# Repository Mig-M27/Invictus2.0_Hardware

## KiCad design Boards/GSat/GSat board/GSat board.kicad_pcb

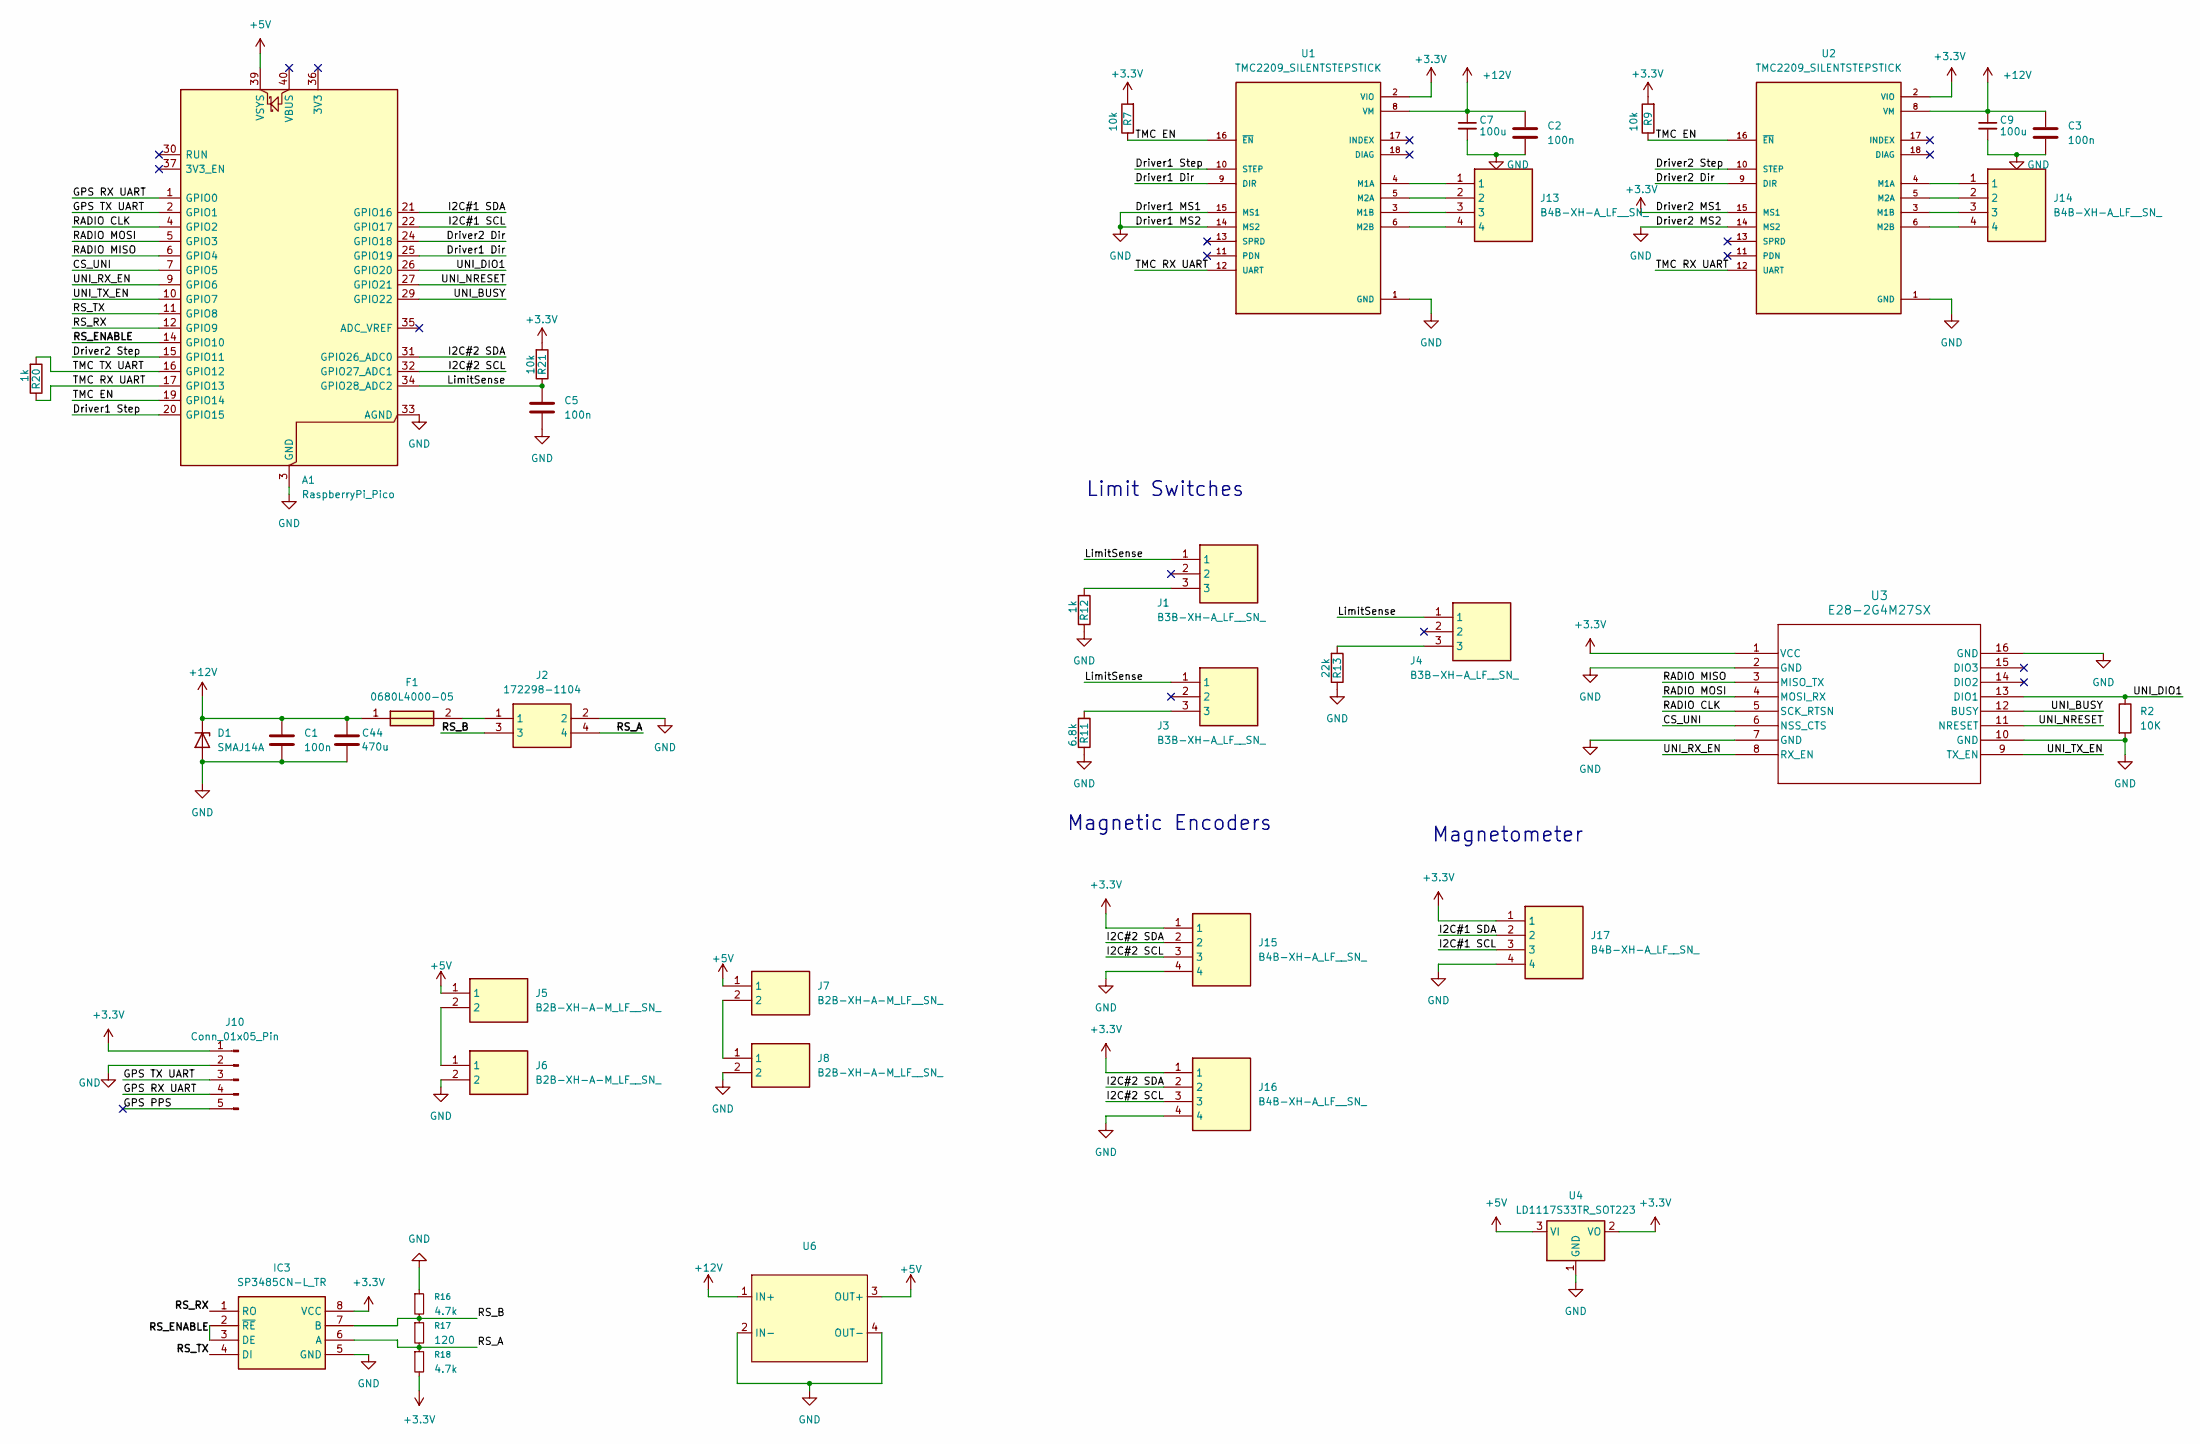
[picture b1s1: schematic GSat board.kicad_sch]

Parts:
A1: RaspberryPi_Pico; RaspberryPi_Pico_Common_Unspecified
C1, C2, C3, C5: 100n; C_0603_1608Metric_Pad1.08x0.95mm_HandSolder
C7, C9: 100u; CP_Elec_6.3x7.7
C44: 470u; CP_Elec_10x10
D1: SMAJ14A; D_SMB
F1: 0680L4000-05; Fuse_2512_6332Metric; Mouser Part Number 530-0ABB-6000-TM
IC3: SP3485CN-L_TR; SOIC127P600X175-8N; Mouser Part Number 701-SP3485CN-L/TR
J1, J3, J4: B3B-XH-A_LF__SN_; B3BXHALFSN; Mouser Part Number 306-B3BXHALFSNP
J2: 172298-1104; 172298-YY04; Mouser Part Number 538-172298-1104
J5, J6, J7, J8: B2B-XH-A-M_LF__SN_; B2BXHAMLFSN; Mouser Part Number 306-B2B-XH-A-MLFS
J10: Conn_01x05_Pin; PinSocket_1x05_P2.54mm_Vertical
J13, J14, J15, J16, J17: B4B-XH-A_LF__SN_; B4BXHALFSN; Mouser Part Number 306-B4BXHALFSN
R2: 10K; R_0603_1608Metric_Pad0.98x0.95mm_HandSolder
R7, R9, R21: 10k; R_0603_1608Metric_Pad0.98x0.95mm_HandSolder
R11: 6.8k; R_0603_1608Metric_Pad0.98x0.95mm_HandSolder
R12, R20: 1k; R_0603_1608Metric_Pad0.98x0.95mm_HandSolder
R13: 22k; R_0603_1608Metric_Pad0.98x0.95mm_HandSolder
R16, R18: 4.7k; R_0603_1608Metric_Pad0.98x0.95mm_HandSolder
R17: 120; R_0603_1608Metric_Pad0.98x0.95mm_HandSolder
U1, U2: TMC2209_SILENTSTEPSTICK; MODULE_TMC2209_SILENTSTEPSTICK; PARTREV 1.20
U3: E28-2G4M27SX; Radio_Module_PST
U4: LD1117S33TR_SOT223; SOT-223-3_TabPin2
U6: DCDC_Module

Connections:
+3.3V: IC3.8 (VCC), J10.1, J15.1, J16.1, J17.1, R7.2, R9.2, R18.2, R21.2, U1.2 (VIO), U2.2 (VIO), U2.15 (MS1), U3.1 (VCC), U4.2 (VO)
+5V: A1.39 (VSYS), J5.1, J7.1, U4.3 (VI), U6.3 (OUT+)
+12V: C1.1, C2.1, C3.1, C7.1, C9.1, C44.1, D1.1 (K), F1.1, U1.8 (VM), U2.8 (VM), U6.1 (IN+)
/CS_UNI: A1.7 (GPIO5), U3.6 (NSS_CTS)
/Driver1 Dir: A1.25 (GPIO19), U1.9 (DIR)
/Driver1 Step: A1.20 (GPIO15), U1.10 (STEP)
/Driver2 Dir: A1.24 (GPIO18), U2.9 (DIR)
/Driver2 Step: A1.15 (GPIO11), U2.10 (STEP)
/GPS PPS: J10.5
/GPS RX UART: A1.1 (GPIO0), J10.4
/GPS TX UART: A1.2 (GPIO1), J10.3
/I2C#1 SCL: A1.22 (GPIO17), J17.3
/I2C#1 SDA: A1.21 (GPIO16), J17.2
/I2C#2 SCL: A1.32 (GPIO27_ADC1), J15.3, J16.3
/I2C#2 SDA: A1.31 (GPIO26_ADC0), J15.2, J16.2
/LimitSense: A1.34 (GPIO28_ADC2), C5.1, J1.1, J3.1, J4.1, R21.1
/RADIO CLK: A1.4 (GPIO2), U3.5 (SCK_RTSN)
/RADIO MISO: A1.6 (GPIO4), U3.3 (MISO_TX)
/RADIO MOSI: A1.5 (GPIO3), U3.4 (MOSI_RX)
/RS_A: IC3.6 (A), J2.4, R17.2, R18.1
/RS_B: IC3.7 (B), J2.3, R16.2, R17.1
/RS_ENABLE: A1.14 (GPIO10), IC3.2 (~RE), IC3.3 (DE)
/RS_RX: A1.12 (GPIO9), IC3.1 (RO)
/RS_TX: A1.11 (GPIO8), IC3.4 (DI)
/TMC EN: A1.19 (GPIO14), R7.1, R9.1, U1.16 (~EN), U2.16 (~EN)
/TMC RX UART: A1.17 (GPIO13), R20.1, U1.12 (UART), U2.12 (UART)
/TMC TX UART: A1.16 (GPIO12), R20.2
/UNI_BUSY: A1.29 (GPIO22), U3.12 (BUSY)
/UNI_DIO1: A1.26 (GPIO20), R2.1, U3.13 (DIO1)
/UNI_NRESET: A1.27 (GPIO21), U3.11 (NRESET)
/UNI_RX_EN: A1.9 (GPIO6), U3.8 (RX_EN)
/UNI_TX_EN: A1.10 (GPIO7), U3.9 (TX_EN)
GND: A1.3 (GND), A1.8 (GND), A1.13 (GND), A1.18 (GND), A1.23 (GND), A1.28 (GND), A1.33 (AGND), A1.38 (GND), C1.2, C2.2, C3.2, C5.2, C7.2, C9.2, C44.2, D1.2 (A), IC3.5 (GND), J2.2, J6.2, J8.2, J10.2, J15.4, J16.4, J17.4, R2.2, R11.1, R12.1, R13.1, R16.1, U1.1 (GND), U1.7 (GND), U1.14 (MS2), U1.15 (MS1), U2.1 (GND), U2.7 (GND), U2.14 (MS2), U3.2 (GND), U3.7 (GND), U3.10 (GND), U3.16 (GND), U4.1 (GND), U6.2 (IN-), U6.4 (OUT-)
unnamed: F1.2, J2.1
unnamed: J1.3, R12.2
unnamed: J3.3, R11.2
unnamed: J4.3, R13.2
unnamed: J5.2, J6.1
unnamed: J7.2, J8.1
unnamed: J13.1, U1.4 (M1A)
unnamed: J13.3, U1.3 (M1B)
unnamed: J13.2, U1.5 (M2A)
unnamed: J13.4, U1.6 (M2B)
unnamed: J14.1, U2.4 (M1A)
unnamed: J14.3, U2.3 (M1B)
unnamed: J14.2, U2.5 (M2A)
unnamed: J14.4, U2.6 (M2B)

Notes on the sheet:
Magnetic Encoders
Limit Switches
Magnetometer

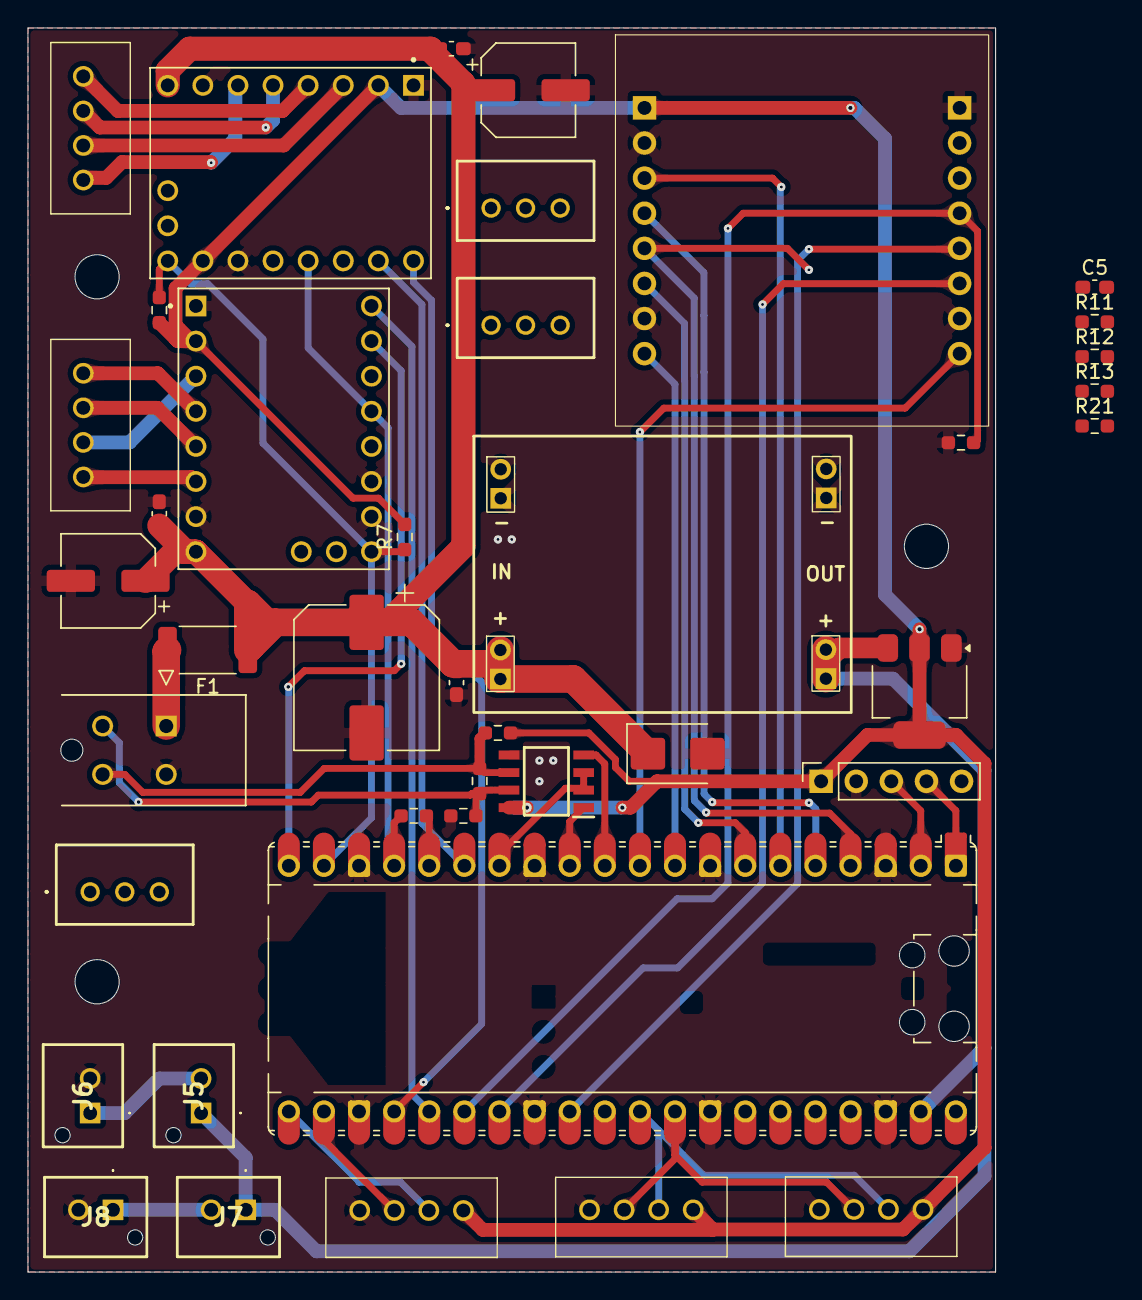
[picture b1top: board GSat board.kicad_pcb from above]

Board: 2 copper layers, 70.0 x 90.0 mm, 41 parts (0 on the bottom side), 46 nets.
